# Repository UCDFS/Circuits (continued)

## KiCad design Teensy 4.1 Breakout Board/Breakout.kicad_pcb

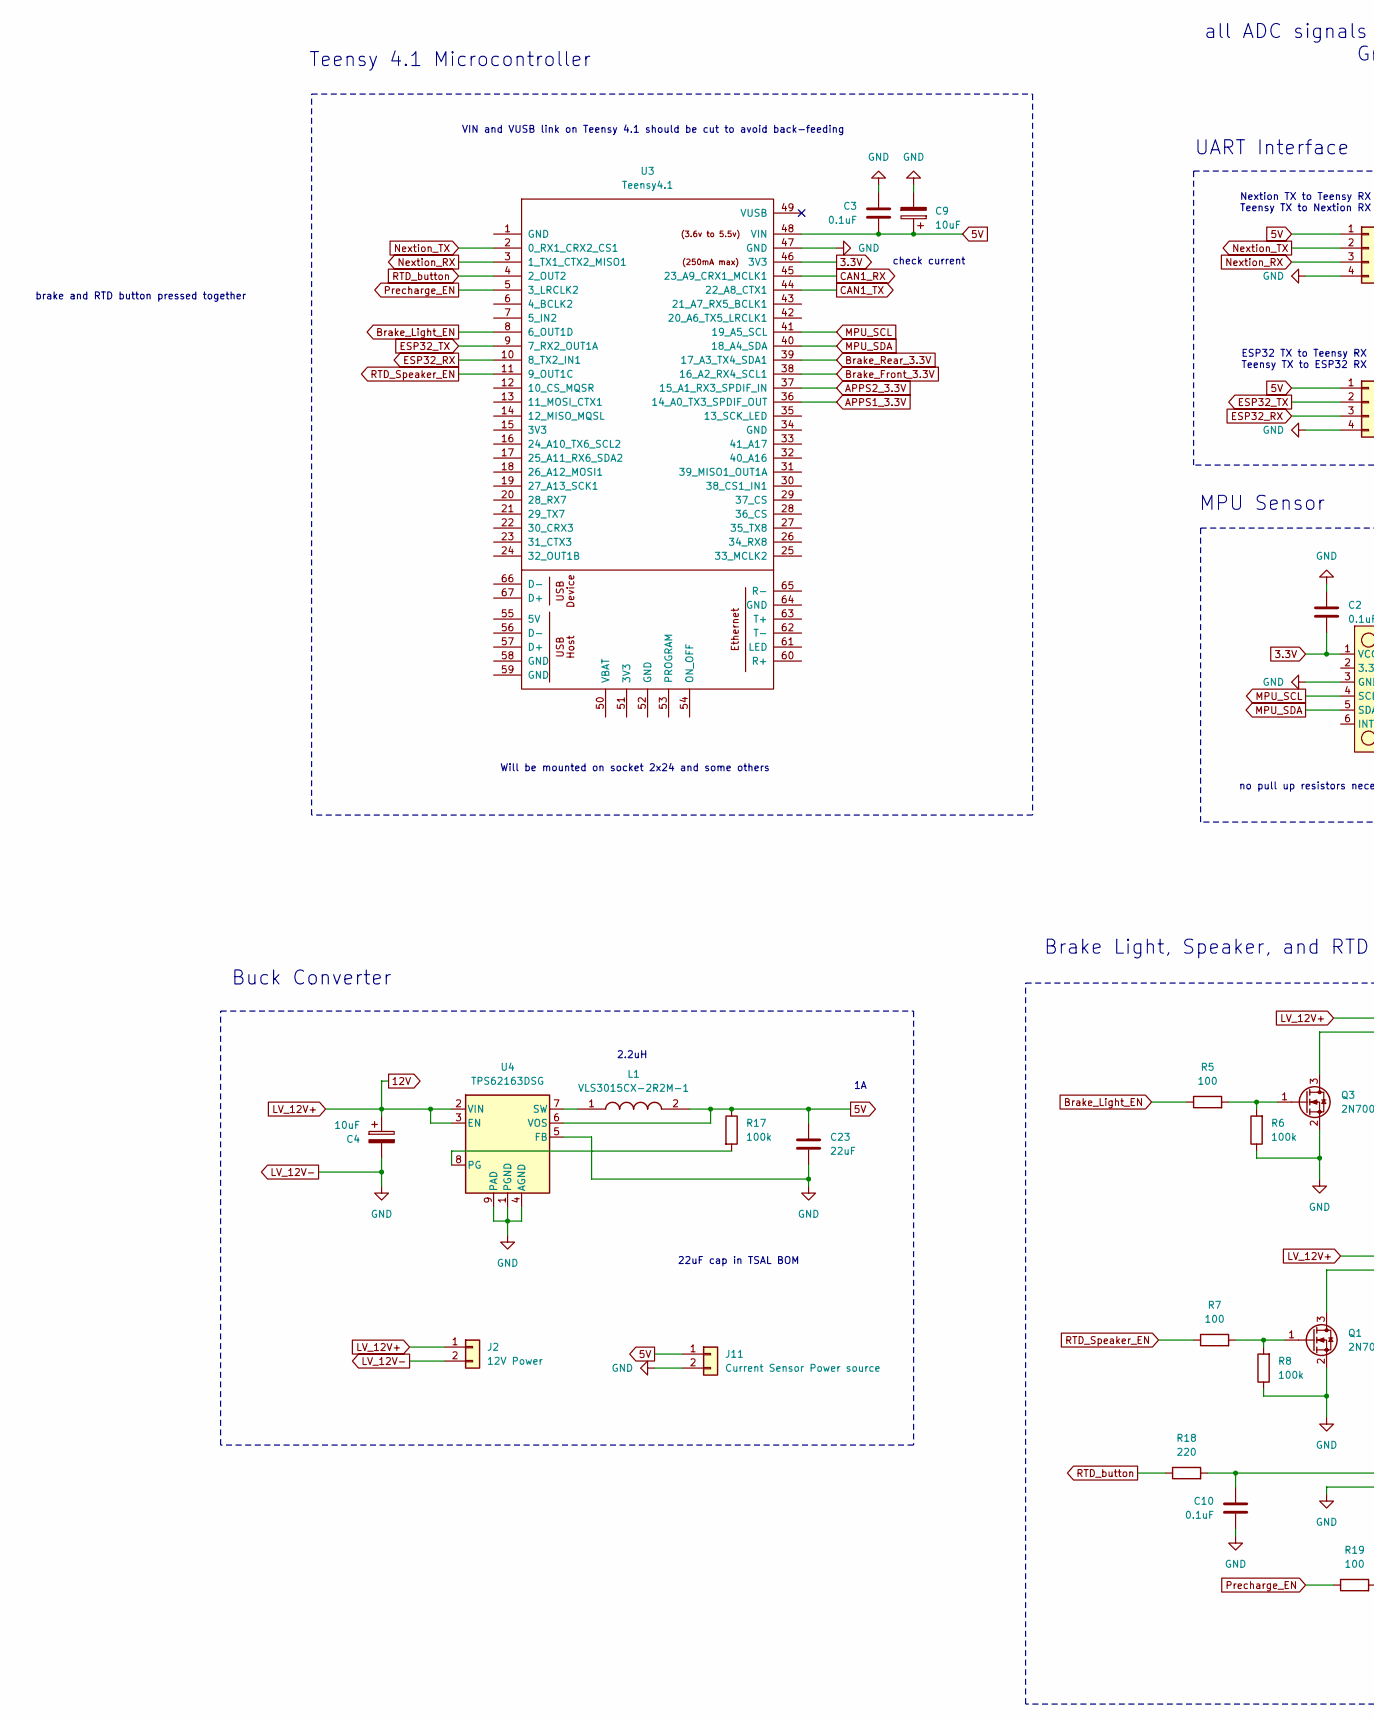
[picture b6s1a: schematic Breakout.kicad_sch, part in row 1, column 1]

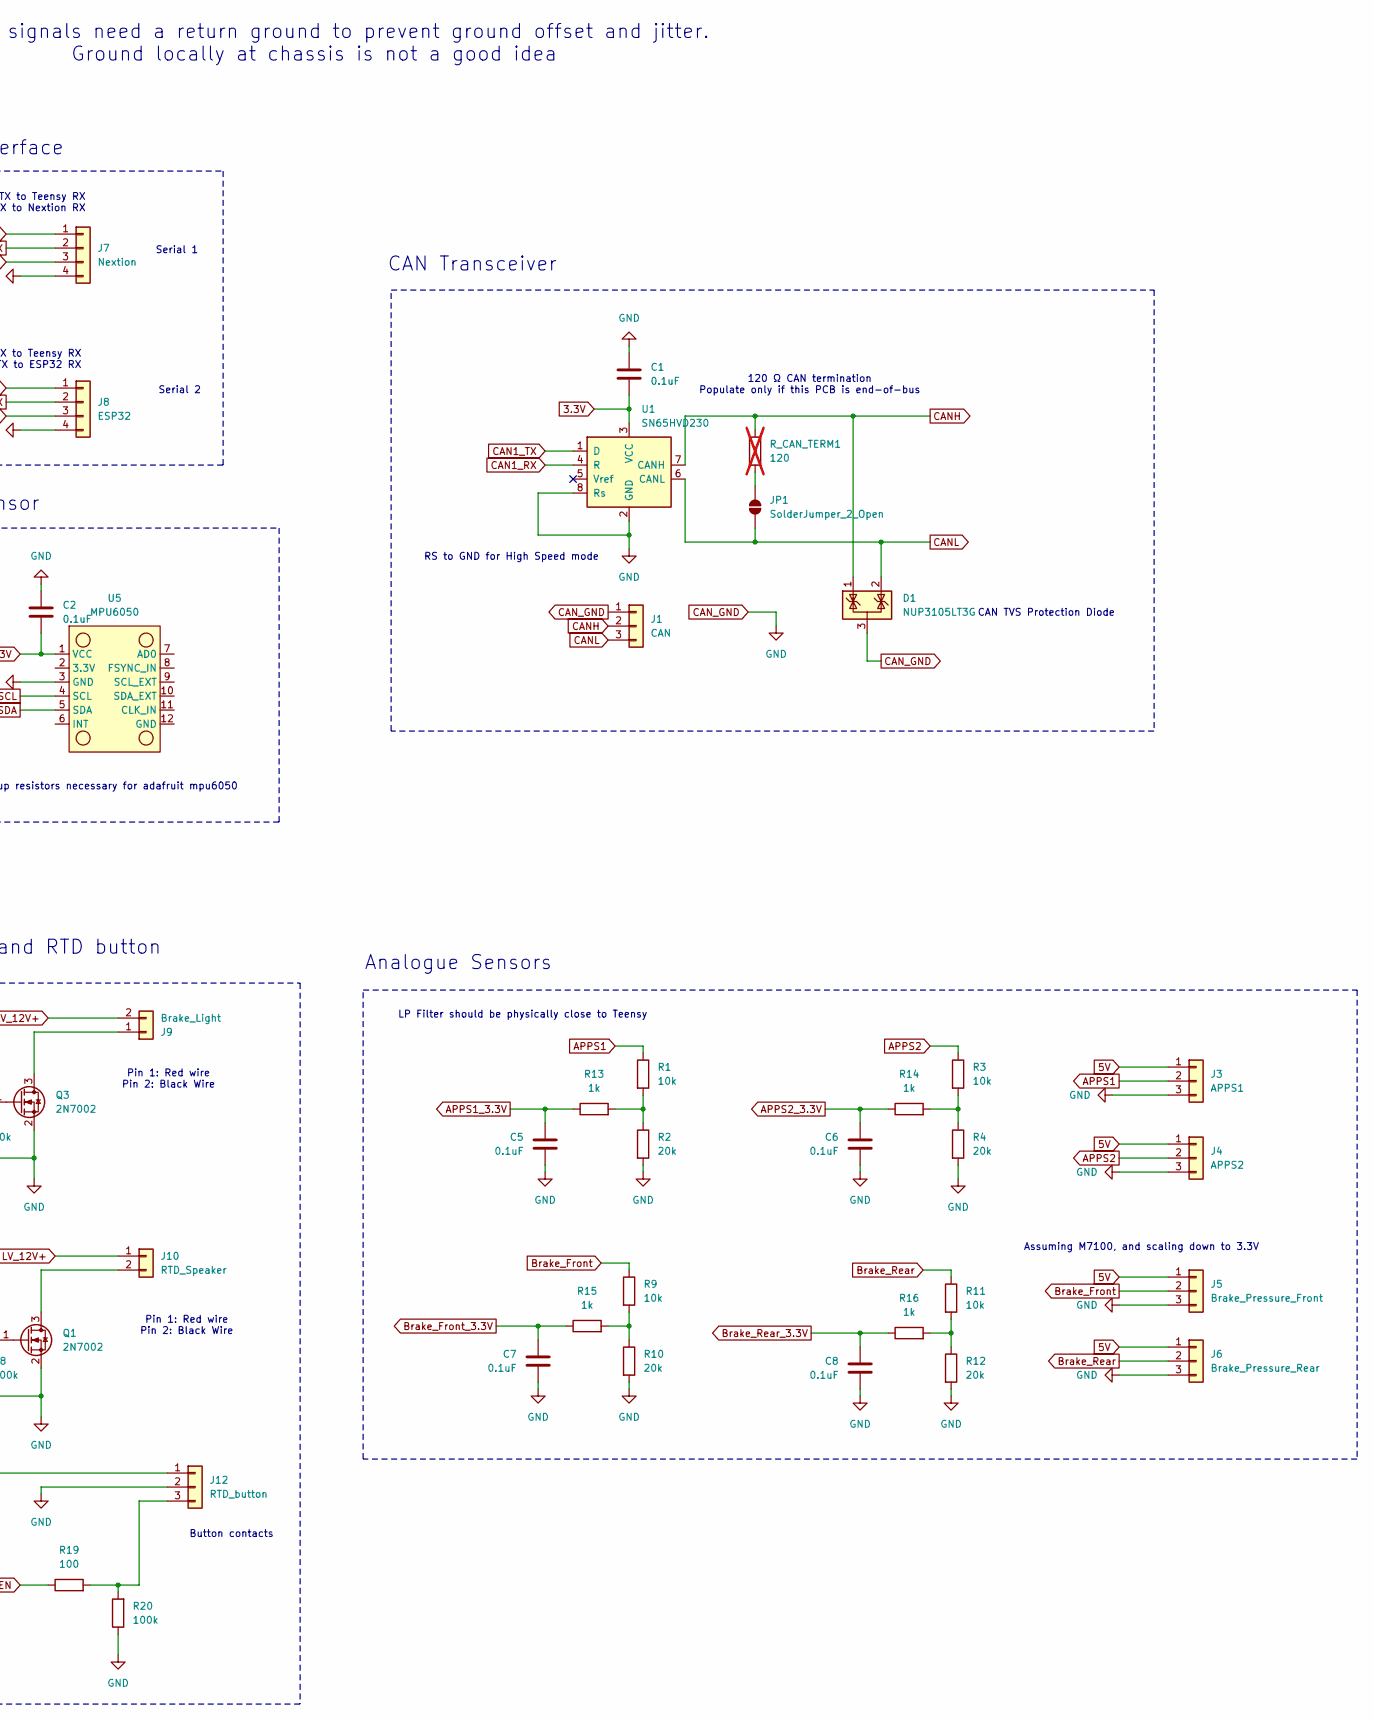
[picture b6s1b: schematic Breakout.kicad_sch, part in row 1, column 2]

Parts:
C1, C2, C3, C5, C6, C7, C8, C10: 0.1uF; FA18X7R1H104KNU00
C4, C9: 10uF; CP_Radial_D5.0mm_P2.50mm; Part Number ECE-A1EKA100I
C23: 22uF; RDEC71E226K3P1H03B; Part Number RDEC71E226K3P1H03B
D1: NUP3105LT3G; SOT-23
J1: CAN; JST_XH_B3B-XH-A_1x03_P2.50mm_Vertical; Part Number B3B-XH-A
J2: 12V Power; JST_XH_B2B-XH-A_1x02_P2.50mm_Vertical; Part Number B2B-XH-A
J3: APPS1; JST_XH_B3B-XH-A_1x03_P2.50mm_Vertical; Part Number B3B-XH-A
J4: APPS2; JST_XH_B3B-XH-A_1x03_P2.50mm_Vertical; Part Number B3B-XH-A
J5: Brake_Pressure_Front; JST_XH_B3B-XH-A_1x03_P2.50mm_Vertical; Part Number B3B-XH-A
J6: Brake_Pressure_Rear; JST_XH_B3B-XH-A_1x03_P2.50mm_Vertical; Part Number B3B-XH-A
J7: Nextion; JST_XH_B4B-XH-A_1x04_P2.50mm_Vertical; Part Number B4B-XH-A
J8: ESP32; JST_XH_B4B-XH-A_1x04_P2.50mm_Vertical; Part Number B4B-XH-A
J9: Brake_Light; JST_XH_B2B-XH-A_1x02_P2.50mm_Vertical; Part Number B2B-XH-A
J10: RTD_Speaker; JST_XH_B2B-XH-A_1x02_P2.50mm_Vertical; Part Number B2B-XH-A
J11: Current Sensor Power source; JST_XH_B2B-XH-A_1x02_P2.50mm_Vertical; Part Number B2B-XH-A
J12: RTD_button; JST_XH_B3B-XH-A_1x03_P2.50mm_Vertical; Part Number B3B-XH-A
JP1: SolderJumper_2_Open; SolderJumper-2_P1.3mm_Open_Pad1.0x1.5mm
L1: VLS3015CX-2R2M-1; VLS3015; Mouser Part Number 810-VLS3015CX-2R2M-1
Q1, Q3: 2N7002; SOT-23; Part Number 2N7002
R1, R3, R9, R11: 10k; R_Axial_DIN0207_L6.3mm_D2.5mm_P10.16mm_Horizontal; Part Number MCF 0.25W 10K
R2, R4, R10, R12: 20k; R_Axial_DIN0207_L6.3mm_D2.5mm_P10.16mm_Horizontal; Part Number CFR25SJT-52A20K
R5, R7, R19: 100; R_Axial_DIN0207_L6.3mm_D2.5mm_P10.16mm_Horizontal; Part Number MCF 0.25W 100
R6, R8, R17, R20: 100k; R_Axial_DIN0207_L6.3mm_D2.5mm_P10.16mm_Horizontal; Part Number MCF 0.25W 100K
R13, R14, R15, R16: 1k; R_Axial_DIN0207_L6.3mm_D2.5mm_P10.16mm_Horizontal; Part Number MCF 0.25W 1K
R18: 220; R_Axial_DIN0207_L6.3mm_D2.5mm_P10.16mm_Horizontal; Part Number MCF 0.25W 220
R_CAN_TERM1: 120; R_Axial_DIN0207_L6.3mm_D2.5mm_P10.16mm_Horizontal; Part Number MCF 0.25W 120; not fitted
U1: SN65HVD230; SOIC-8_3.9x4.9mm_P1.27mm
U3: Teensy4.1; Teensy41
U4: TPS62163DSG; WSON-8-1EP_2x2mm_P0.5mm_EP0.9x1.6mm_ThermalVias
U5: MPU6050

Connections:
3.3V: C1.2, C2.2, U1.3 (VCC), U3.46 (3V3), U5.1 (VCC)
5V: C3.2, C9.1, C23.2, J3.1, J4.1, J5.1, J6.1, J7.1, J8.1, J11.1, L1.2, R17.1, U3.48 (VIN), U4.6 (VOS)
12V: C4.1, J2.1, J9.2, J10.1, U4.2 (VIN), U4.3 (EN)
APPS1: J3.2, R1.1
APPS1_3.3V: C5.1, R13.1, U3.36 (14_A0_TX3_SPDIF_OUT)
APPS2: J4.2, R3.1
APPS2_3.3V: C6.1, R14.1, U3.37 (15_A1_RX3_SPDIF_IN)
Brake_Front: J5.2, R9.1
Brake_Front_3.3V: C7.1, R15.1, U3.38 (16_A2_RX4_SCL1)
Brake_Light_EN: R5.1, U3.8 (6_OUT1D)
Brake_Rear: J6.2, R11.1
Brake_Rear_3.3V: C8.1, R16.1, U3.39 (17_A3_TX4_SDA1)
CAN1_RX: U1.4 (R), U3.45 (23_A9_CRX1_MCLK1)
CAN1_TX: U1.1 (D), U3.44 (22_A8_CTX1)
CANH: D1.1 (K), J1.2, R_CAN_TERM1.1, U1.7 (CANH)
CANL: D1.2 (K), J1.3, JP1.1 (A), U1.6 (CANL)
CAN_GND: C1.1, C2.1, C3.1, C4.2, C5.2, C6.2, C7.2, C8.2, C9.2, C10.2, C23.1, D1.3 (A), J1.1, J2.2, J3.3, J4.3, J5.3, J6.3, J7.4, J8.4, J11.2, J12.2, Q1.2 (S), Q3.2 (S), R2.2, R4.2, R6.1, R8.1, R10.2, R12.2, R20.1, U1.2 (GND), U1.8 (Rs), U3.47 (GND), U4.1 (PGND), U4.4 (AGND), U4.5 (FB), U4.9 (PAD), U5.3 (GND)
ESP32_RX: J8.3, U3.10 (8_TX2_IN1)
ESP32_TX: J8.2, U3.9 (7_RX2_OUT1A)
MPU_SCL: U3.41 (19_A5_SCL), U5.4 (SCL)
MPU_SDA: U3.40 (18_A4_SDA), U5.5 (SDA)
unnamed: J9.1, Q3.3 (D)
unnamed: J10.2, Q1.3 (D)
unnamed: C10.1, J12.1, R18.2
unnamed: J12.3, R19.2, R20.2
unnamed: JP1.2 (B), R_CAN_TERM1.2
unnamed: Q1.1 (G), R7.2, R8.2
unnamed: Q3.1 (G), R5.2, R6.2
unnamed: R1.2, R2.1, R13.2
unnamed: R9.2, R10.1, R15.2
unnamed: R11.2, R12.1, R16.2
unnamed: R3.2, R4.1, R14.2
unnamed: R17.2, U4.8 (PG)
unnamed: L1.1, U4.7 (SW)
Nextion_RX: J7.3, U3.3 (1_TX1_CTX2_MISO1)
Nextion_TX: J7.2, U3.2 (0_RX1_CRX2_CS1)
Precharge_EN: R19.1, U3.5 (3_LRCLK2)
RTD_Speaker_EN: R7.1, U3.11 (9_OUT1C)
RTD_button: R18.1, U3.4 (2_OUT2)

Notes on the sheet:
2.2uH
brake and RTD button pressed together
Nextion TX to Teensy RX Teensy TX to Nextion RX
LP Filter should be physically close to Teensy
RS to GND for High Speed mode
120 Ω CAN termination Populate only if this PCB is end-of-bus
check current
Brake Light, Speaker, and RTD button
UART Interface
Analogue Sensors
Serial 1
Button contacts
MPU Sensor
VIN and VUSB link on Teensy 4.1 should be cut to avoid back-feeding
Serial 2
no pull up resistors necessary for adafruit mpu6050
22uF cap in TSAL BOM
CAN TVS Protection Diode
Will be mounted on socket 2x24 and some others
Assuming M7100, and scaling down to 3.3V
Pin 1: Red wire Pin 2: Black Wire
CAN Transceiver
ESP32 TX to Teensy RX Teensy TX to ESP32 RX
Teensy 4.1 Microcontroller
Buck Converter
all ADC signals need a return ground to prevent ground offset and jitter. Ground locally at chassis is not a good idea

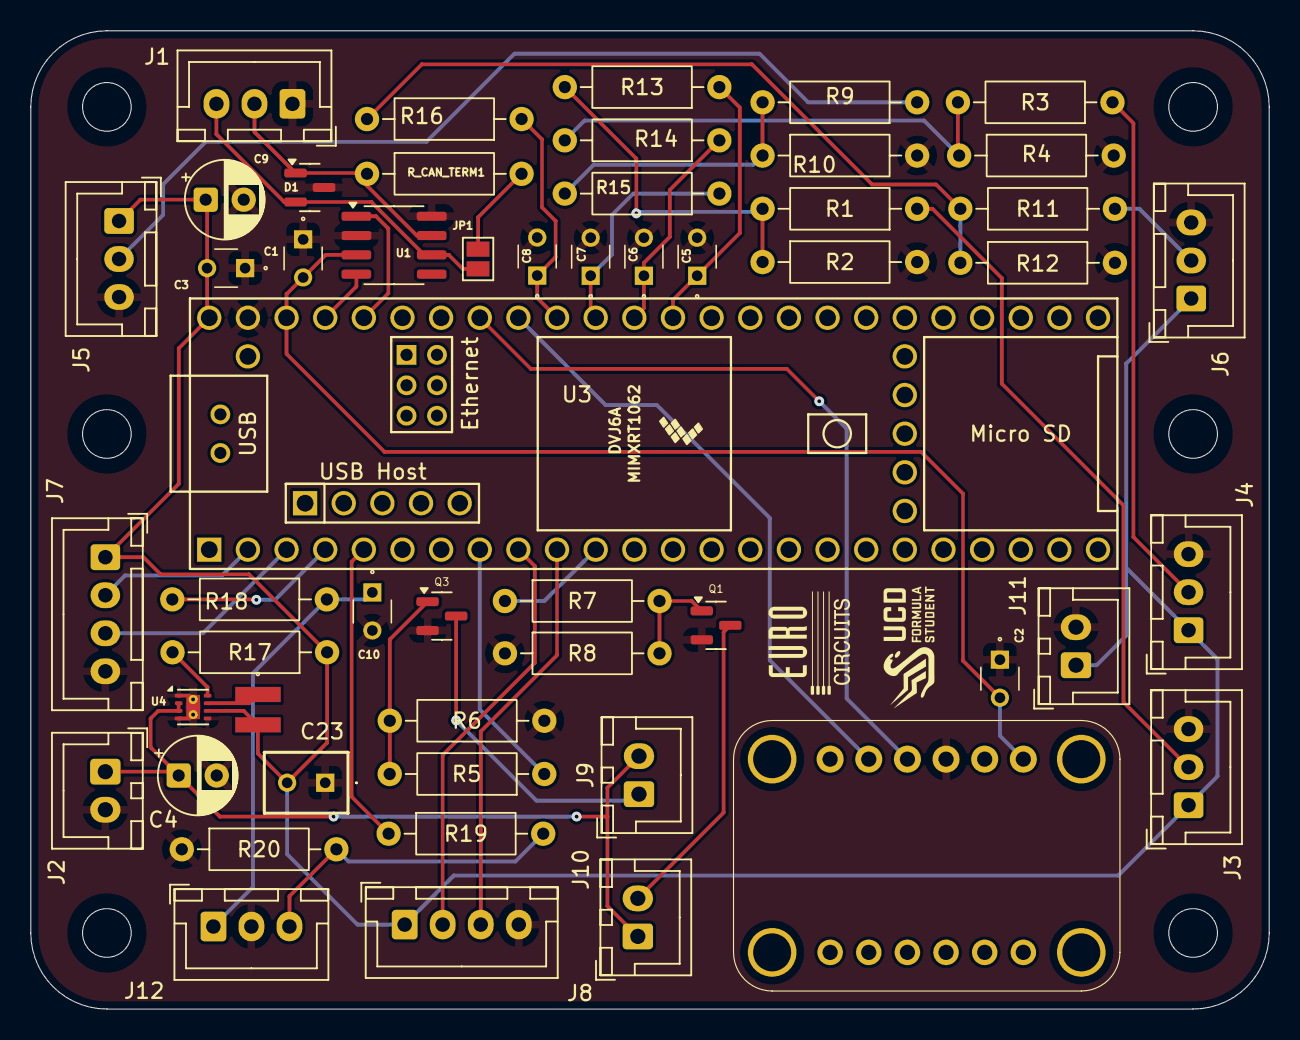
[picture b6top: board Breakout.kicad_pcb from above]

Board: 2 copper layers, 81.4 x 64.3 mm, 53 parts (0 on the bottom side), 39 nets.
